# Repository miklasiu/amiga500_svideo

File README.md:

I've just made it - there are errors :) I'll update sometime when I find the time. Generally it works. Basically red and blue are swapped on the AD724 input (oops) and input resistor divider needs to be adjusted to increase voltage a bit. Also AD724 input resistors need to have larger values to decrease current draw.

# amiga500_svideo
 Luma Chroma output from A500

GGLabs A520HD redraw with AD724 based SVIDEO.

Connector PCB to fit on the right side behind the floppy.

To keep the video port operational I will do high impedance input (not 75 ohm) tap directly to video hybrid circuit and adjust input level via resistor divider. 
The same applies to AD724. It needs 714mVpp so I _think_ it needs 1/2nd of the A500HD output. But we shall see.

Work in progress.

BTW - I just bought my 1st Amiga in 2022. So I am ~30years behind. Catching up. 
Just noticed all mods cost more than A500. It seems cheaper and surely funnier to do them myself.
Fortunately my A500 is broken so more projects coming as original parts are expensive too :D

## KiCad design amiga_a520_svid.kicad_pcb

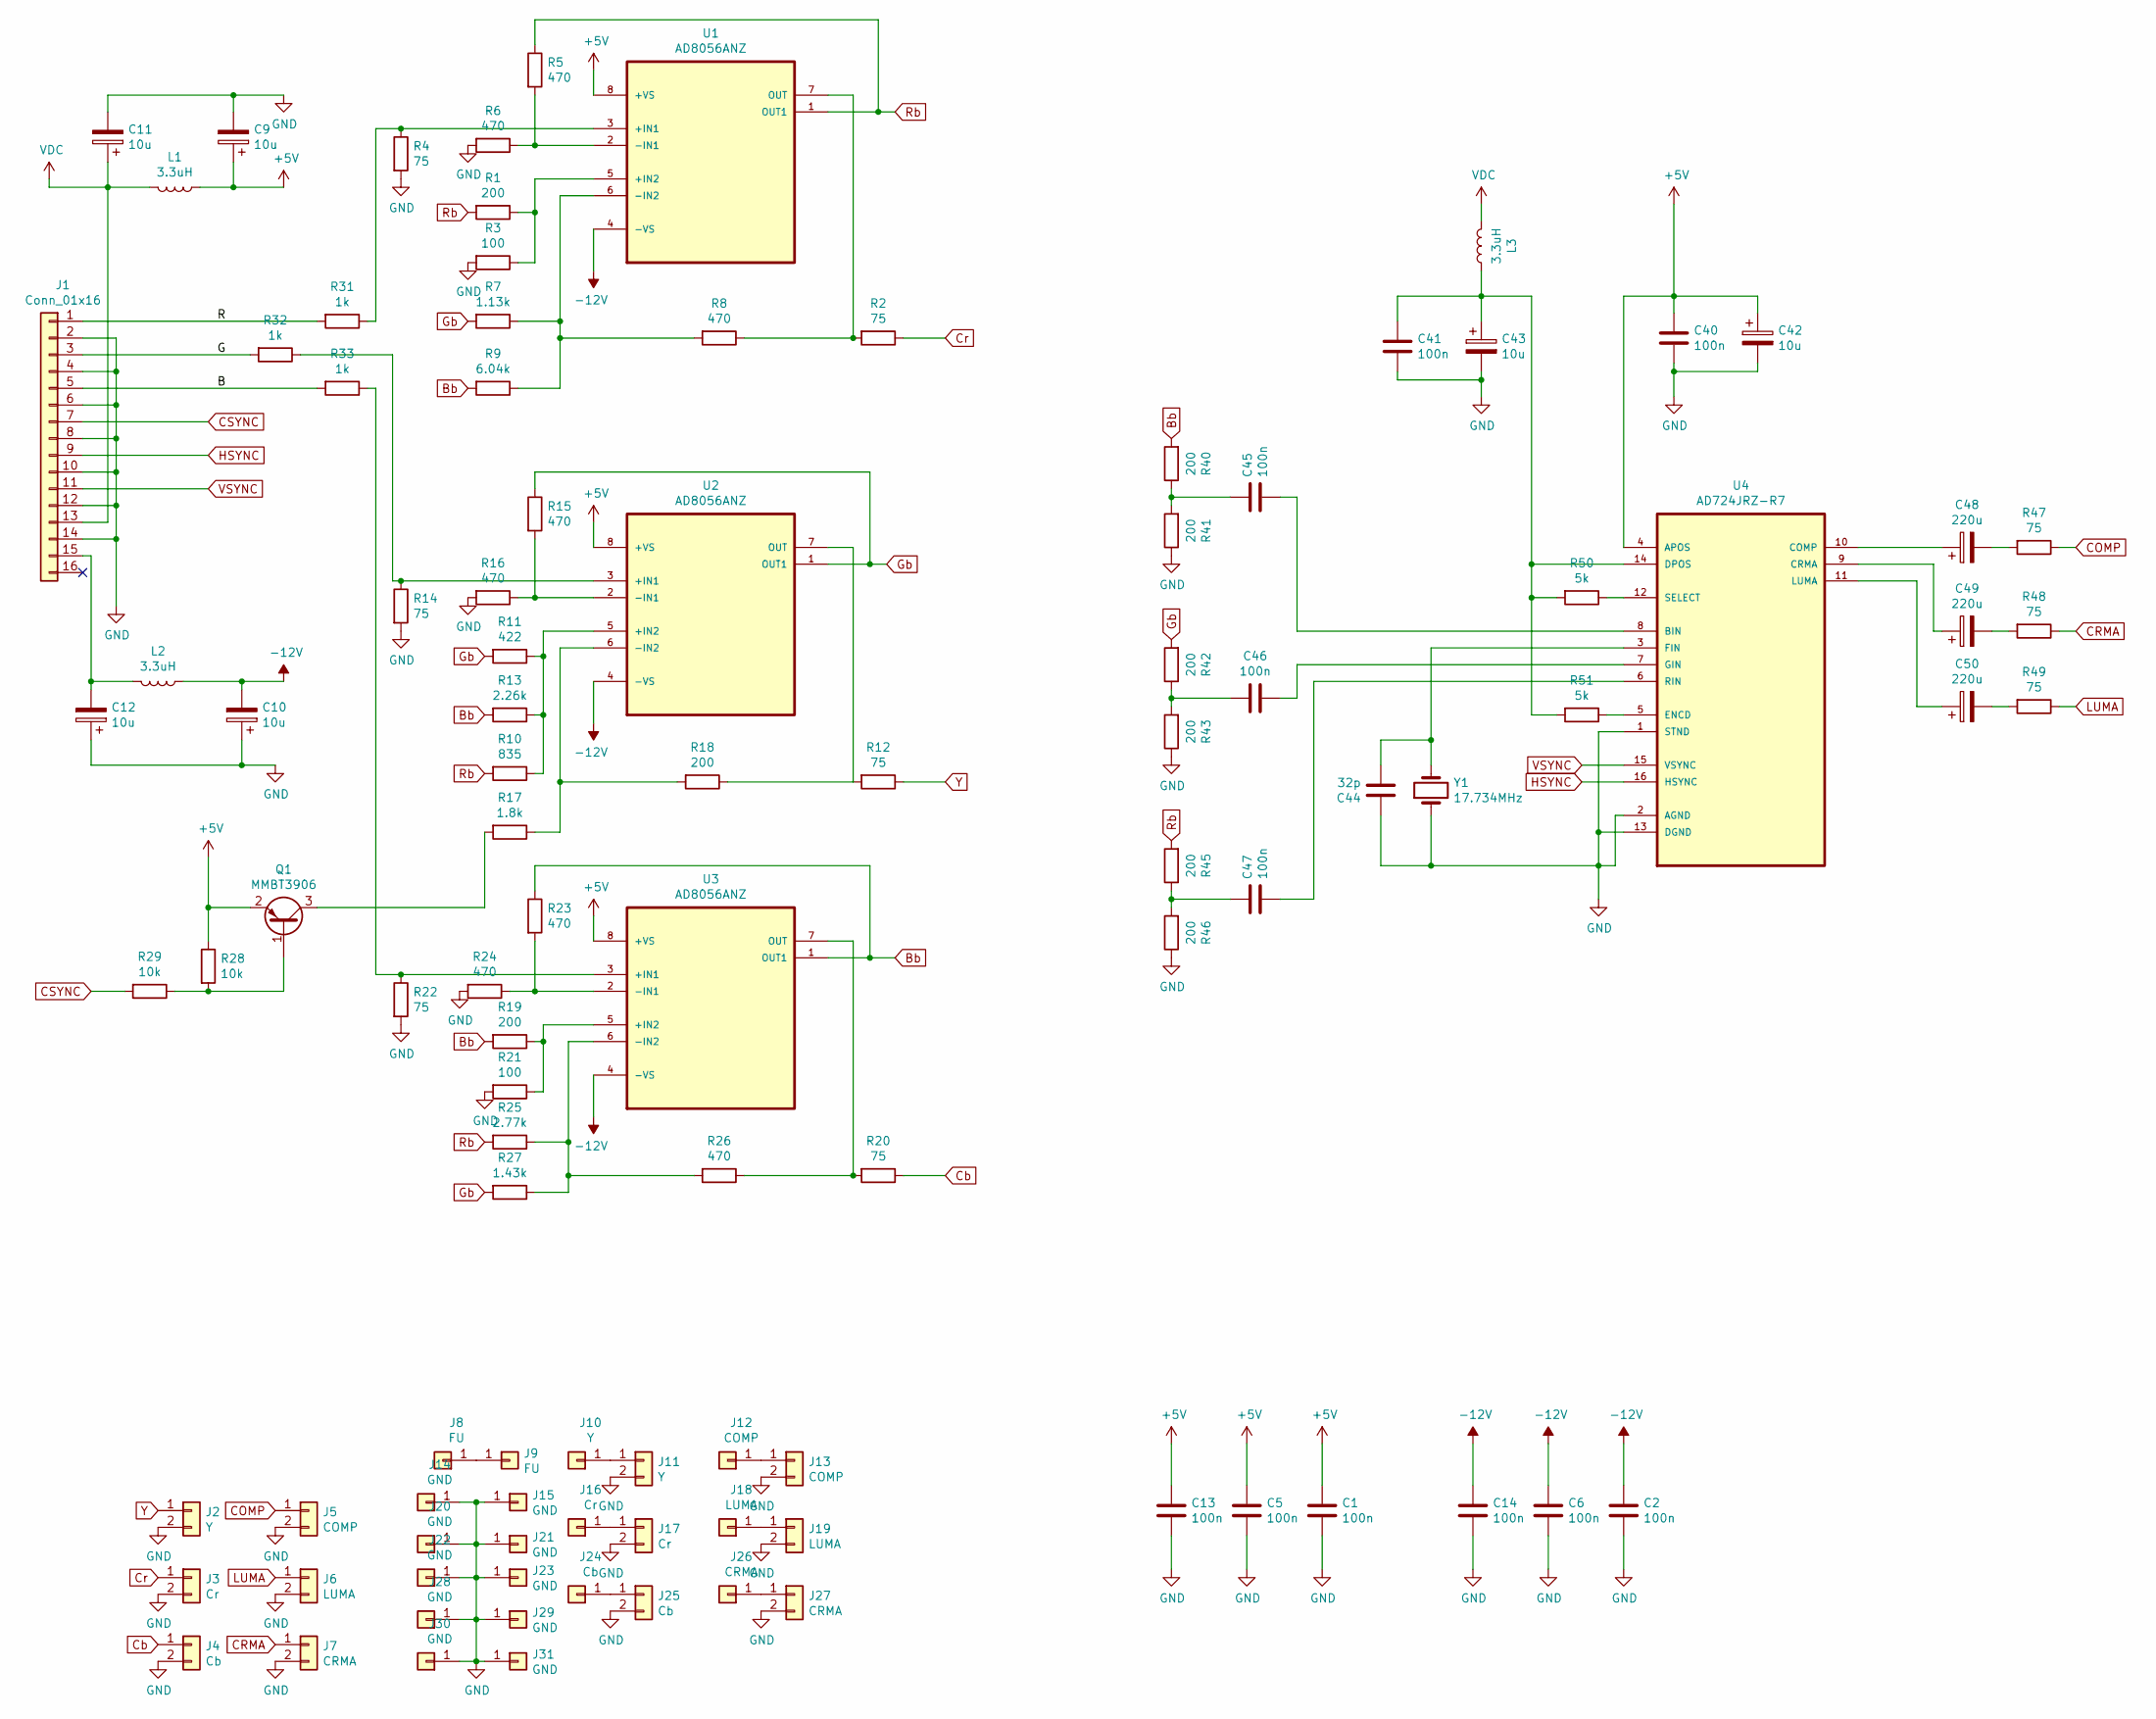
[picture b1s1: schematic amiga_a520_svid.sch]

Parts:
C1, C2, C5, C6, C13, C14, C40, C41, C45, C46, C47: 100n; C_1206_3216Metric_Pad1.33x1.80mm_HandSolder
C9, C10, C11, C12, C42, C43: 10u; CP_Elec_5x5.4
C44: 32p; C_1206_3216Metric_Pad1.33x1.80mm_HandSolder
C48, C49, C50: 220u; CP_Elec_6.3x7.7
J1: Conn_01x16; PinHeader_1x16_P1.27mm_Vertical_SMD_Pin1Left
J2, J11: Y; PinHeader_1x02_P2.54mm_Vertical
J3, J17: Cr; PinHeader_1x02_P2.54mm_Vertical
J4, J25: Cb; PinHeader_1x02_P2.54mm_Vertical
J5, J13: COMP; PinHeader_1x02_P2.54mm_Vertical
J6, J19: LUMA; PinHeader_1x02_P2.54mm_Vertical
J7, J27: CRMA; PinHeader_1x02_P2.54mm_Vertical
J8, J9: FU; Pin_D0.9mm_L10.0mm_W2.4mm_FlatFork
J10: Y; Pin_D0.9mm_L10.0mm_W2.4mm_FlatFork
J12: COMP; Pin_D0.9mm_L10.0mm_W2.4mm_FlatFork
J14, J15, J20, J21, J22, J23, J28, J29, J30, J31: GND; Pin_D0.9mm_L10.0mm_W2.4mm_FlatFork
J16: Cr; Pin_D0.9mm_L10.0mm_W2.4mm_FlatFork
J18: LUMA; Pin_D0.9mm_L10.0mm_W2.4mm_FlatFork
J24: Cb; Pin_D0.9mm_L10.0mm_W2.4mm_FlatFork
J26: CRMA; Pin_D0.9mm_L10.0mm_W2.4mm_FlatFork
L1, L2, L3: 3.3uH; L_Axial_L7.0mm_D3.3mm_P10.16mm_Horizontal_Fastron_MICC
Q1: MMBT3906; SOT-23
R1, R18, R19, R40, R41, R42, R43, R45, R46: 200; R_1206_3216Metric_Pad1.30x1.75mm_HandSolder
R2, R4, R12, R14, R20, R22, R47, R48, R49: 75; R_1206_3216Metric_Pad1.30x1.75mm_HandSolder
R3, R21: 100; R_1206_3216Metric_Pad1.30x1.75mm_HandSolder
R5, R6, R8, R15, R16, R23, R24, R26: 470; R_1206_3216Metric_Pad1.30x1.75mm_HandSolder
R7: 1.13k; R_1206_3216Metric_Pad1.30x1.75mm_HandSolder
R9: 6.04k; R_1206_3216Metric_Pad1.30x1.75mm_HandSolder
R10: 835; R_1206_3216Metric_Pad1.30x1.75mm_HandSolder
R11: 422; R_1206_3216Metric_Pad1.30x1.75mm_HandSolder
R13: 2.26k; R_1206_3216Metric_Pad1.30x1.75mm_HandSolder
R17: 1.8k; R_1206_3216Metric_Pad1.30x1.75mm_HandSolder
R25: 2.77k; R_1206_3216Metric_Pad1.30x1.75mm_HandSolder
R27: 1.43k; R_1206_3216Metric_Pad1.30x1.75mm_HandSolder
R28, R29: 10k; R_1206_3216Metric_Pad1.30x1.75mm_HandSolder
R31, R32, R33: 1k; R_1206_3216Metric_Pad1.30x1.75mm_HandSolder
R50, R51: 5k; R_1206_3216Metric_Pad1.30x1.75mm_HandSolder
U1, U2, U3: AD8056ANZ; DIP-8_W7.62mm_SOIC-8; MPN AD8056ANZ
U4: AD724JRZ-R7; SOIC-16W_7.5x10.3mm_P1.27mm; MPN AD724JRZ-R7
Y1: 17.734MHz; Resonator-2Pin_W10.0mm_H5.0mm

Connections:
+5V: C1.1, C5.1, C9.1, C13.1, C40.1, C42.1, L1.1, Q1.2 (E), R28.1, U1.8 (+VS), U2.8 (+VS), U3.8 (+VS), U4.4 (APOS)
-12V: C2.1, C6.1, C10.2, C14.1, L2.1, U1.4 (-VS), U2.4 (-VS), U3.4 (-VS)
/B: J1.5, R33.2
/G: J1.3, R32.2
/R: J1.1, R31.2
Bb: R9.2, R13.2, R19.2, R23.1, R40.2, U3.1 (OUT1)
COMP: J5.1, R47.1
CRMA: J7.1, R48.1
CSYNC: J1.7, R29.2
Cb: J4.1, R20.1
Cr: J3.1, R2.1
GND: C1.2, C2.2, C5.2, C6.2, C9.2, C10.1, C11.2, C12.1, C13.2, C14.2, C40.2, C41.2, C42.2, C43.2, C44.1, J1.2, J1.4, J1.6, J1.8, J1.10, J1.12, J1.14, J2.2, J3.2, J4.2, J5.2, J6.2, J7.2, J11.2, J13.2, J14.1, J15.1, J17.2, J19.2, J20.1, J21.1, J22.1, J23.1, J25.2, J27.2, J28.1, J29.1, J30.1, J31.1, R3.2, R4.2, R6.2, R14.2, R16.2, R21.2, R22.2, R24.2, R41.1, R43.1, R46.1, U4.1 (STND), U4.2 (AGND), U4.13 (DGND), Y1.1
Gb: R7.2, R11.2, R15.1, R27.2, R42.2, U2.1 (OUT1)
HSYNC: J1.9, U4.16 (HSYNC)
LUMA: J6.1, R49.1
unnamed: C12.2, J1.15, L2.2
unnamed: C41.1, C43.1, L3.1, R50.2, R51.2, U4.14 (DPOS)
unnamed: C44.2, U4.3 (FIN), Y1.2
unnamed: C45.1, R40.1, R41.2
unnamed: C45.2, U4.8 (BIN)
unnamed: C46.1, R42.1, R43.2
unnamed: C46.2, U4.7 (GIN)
unnamed: C47.1, R45.1, R46.2
unnamed: C47.2, U4.6 (RIN)
unnamed: C48.1, U4.10 (COMP)
unnamed: C48.2, R47.2
unnamed: C49.1, U4.9 (CRMA)
unnamed: C49.2, R48.2
unnamed: C50.1, U4.11 (LUMA)
unnamed: C50.2, R49.2
unnamed: J8.1, J9.1
unnamed: J10.1, J11.1
unnamed: J12.1, J13.1
unnamed: J16.1, J17.1
unnamed: J18.1, J19.1
unnamed: J24.1, J25.1
unnamed: J26.1, J27.1
unnamed: Q1.1 (B), R28.2, R29.1
unnamed: Q1.3 (C), R17.2
unnamed: R1.1, R3.1, U1.5 (+IN2)
unnamed: R2.2, R8.1, U1.7 (OUT)
unnamed: R5.2, R6.1, U1.2 (-IN1)
unnamed: R7.1, R8.2, R9.1, U1.6 (-IN2)
unnamed: R10.1, R11.1, R13.1, U2.5 (+IN2)
unnamed: R12.2, R18.1, U2.7 (OUT)
unnamed: R14.1, R32.1, U2.3 (+IN1)
unnamed: R15.2, R16.1, U2.2 (-IN1)
unnamed: R17.1, R18.2, U2.6 (-IN2)
unnamed: R19.1, R21.1, U3.5 (+IN2)
unnamed: R20.2, R26.1, U3.7 (OUT)
unnamed: R22.1, R33.1, U3.3 (+IN1)
unnamed: R23.2, R24.1, U3.2 (-IN1)
unnamed: R25.1, R26.2, R27.1, U3.6 (-IN2)
unnamed: R4.1, R31.1, U1.3 (+IN1)
unnamed: R50.1, U4.12 (SELECT)
unnamed: R51.1, U4.5 (ENCD)
Rb: R1.2, R5.1, R10.2, R25.2, R45.2, U1.1 (OUT1)
VDC: C11.1, J1.13, L1.2, L3.2
VSYNC: J1.11, U4.15 (VSYNC)
Y: J2.1, R12.1

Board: 2 copper layers, 104 parts (6 on the bottom side), 60 nets, no tracks yet.

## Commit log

2023-02-12 Initial
2023-02-13 Wider tracks.
    Reroute using wider tracks to help with manual board manufacturing. SVG for printing on transfer material. Mirror F_*
2023-03-20 Fixes after 1st prototype :)
    - Swapped OPAMP outputs :(
    - More careful AD724 implementation
    - MORE SMD! Through hole without metallization is a pain!
